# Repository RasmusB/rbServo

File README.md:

# rbServo Readme

### What is it?
All the hardware and software that is needed to build a CAN-BUS servo controller. It is meant to be used for RC servos.

### What does it contain?

- `3D` - hardware components

- `HW` - all the hardware design files are in this folder

- `SW` - The software for the servo.
 - `rbServoFirmware` - Servo controller firmware

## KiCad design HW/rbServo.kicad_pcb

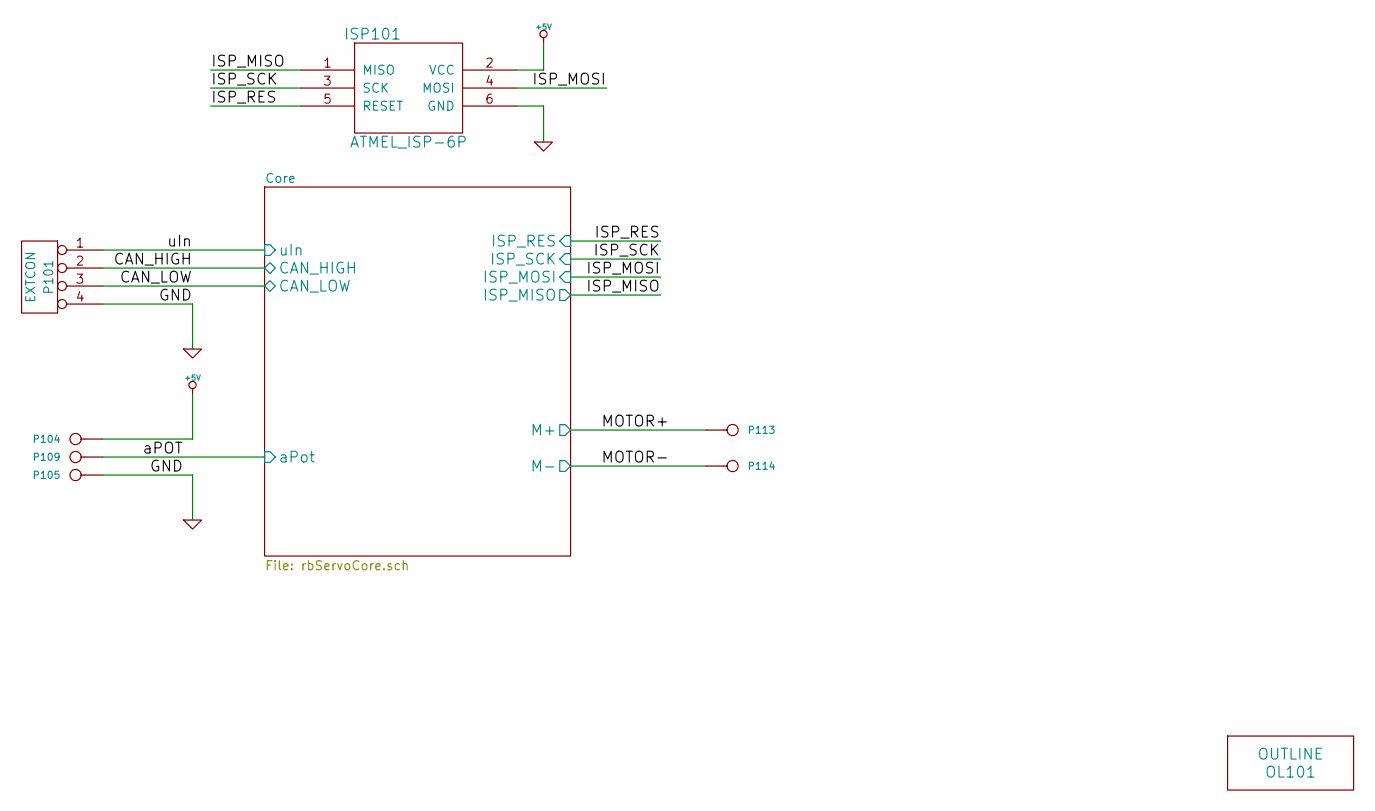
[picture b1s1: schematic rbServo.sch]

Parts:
ISP101: ATMEL_ISP-6P
OL101: OUTLINE
P101: EXTCON
P104: 5V
P105: GND
P109: Pot
P113: M+
P114: M-

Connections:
+5V: ISP101.2 (VCC), P104.1; also elsewhere on the board
/Core/CAN_HIGH: P101.2; also elsewhere on the board
/Core/CAN_LOW: P101.3; also elsewhere on the board
/Core/ISP_MISO: ISP101.1 (MISO); also elsewhere on the board
/Core/ISP_MOSI: ISP101.4 (MOSI); also elsewhere on the board
/Core/ISP_RES: ISP101.5 (RESET); also elsewhere on the board
/Core/ISP_SCK: ISP101.3 (SCK); also elsewhere on the board
/Core/M+: P113.1; also elsewhere on the board
/Core/M-: P114.1; also elsewhere on the board
/Core/aPot: P109.1; also elsewhere on the board
/Core/uIn: P101.1; also elsewhere on the board
GND: ISP101.6 (GND), P101.4, P105.1; also elsewhere on the board

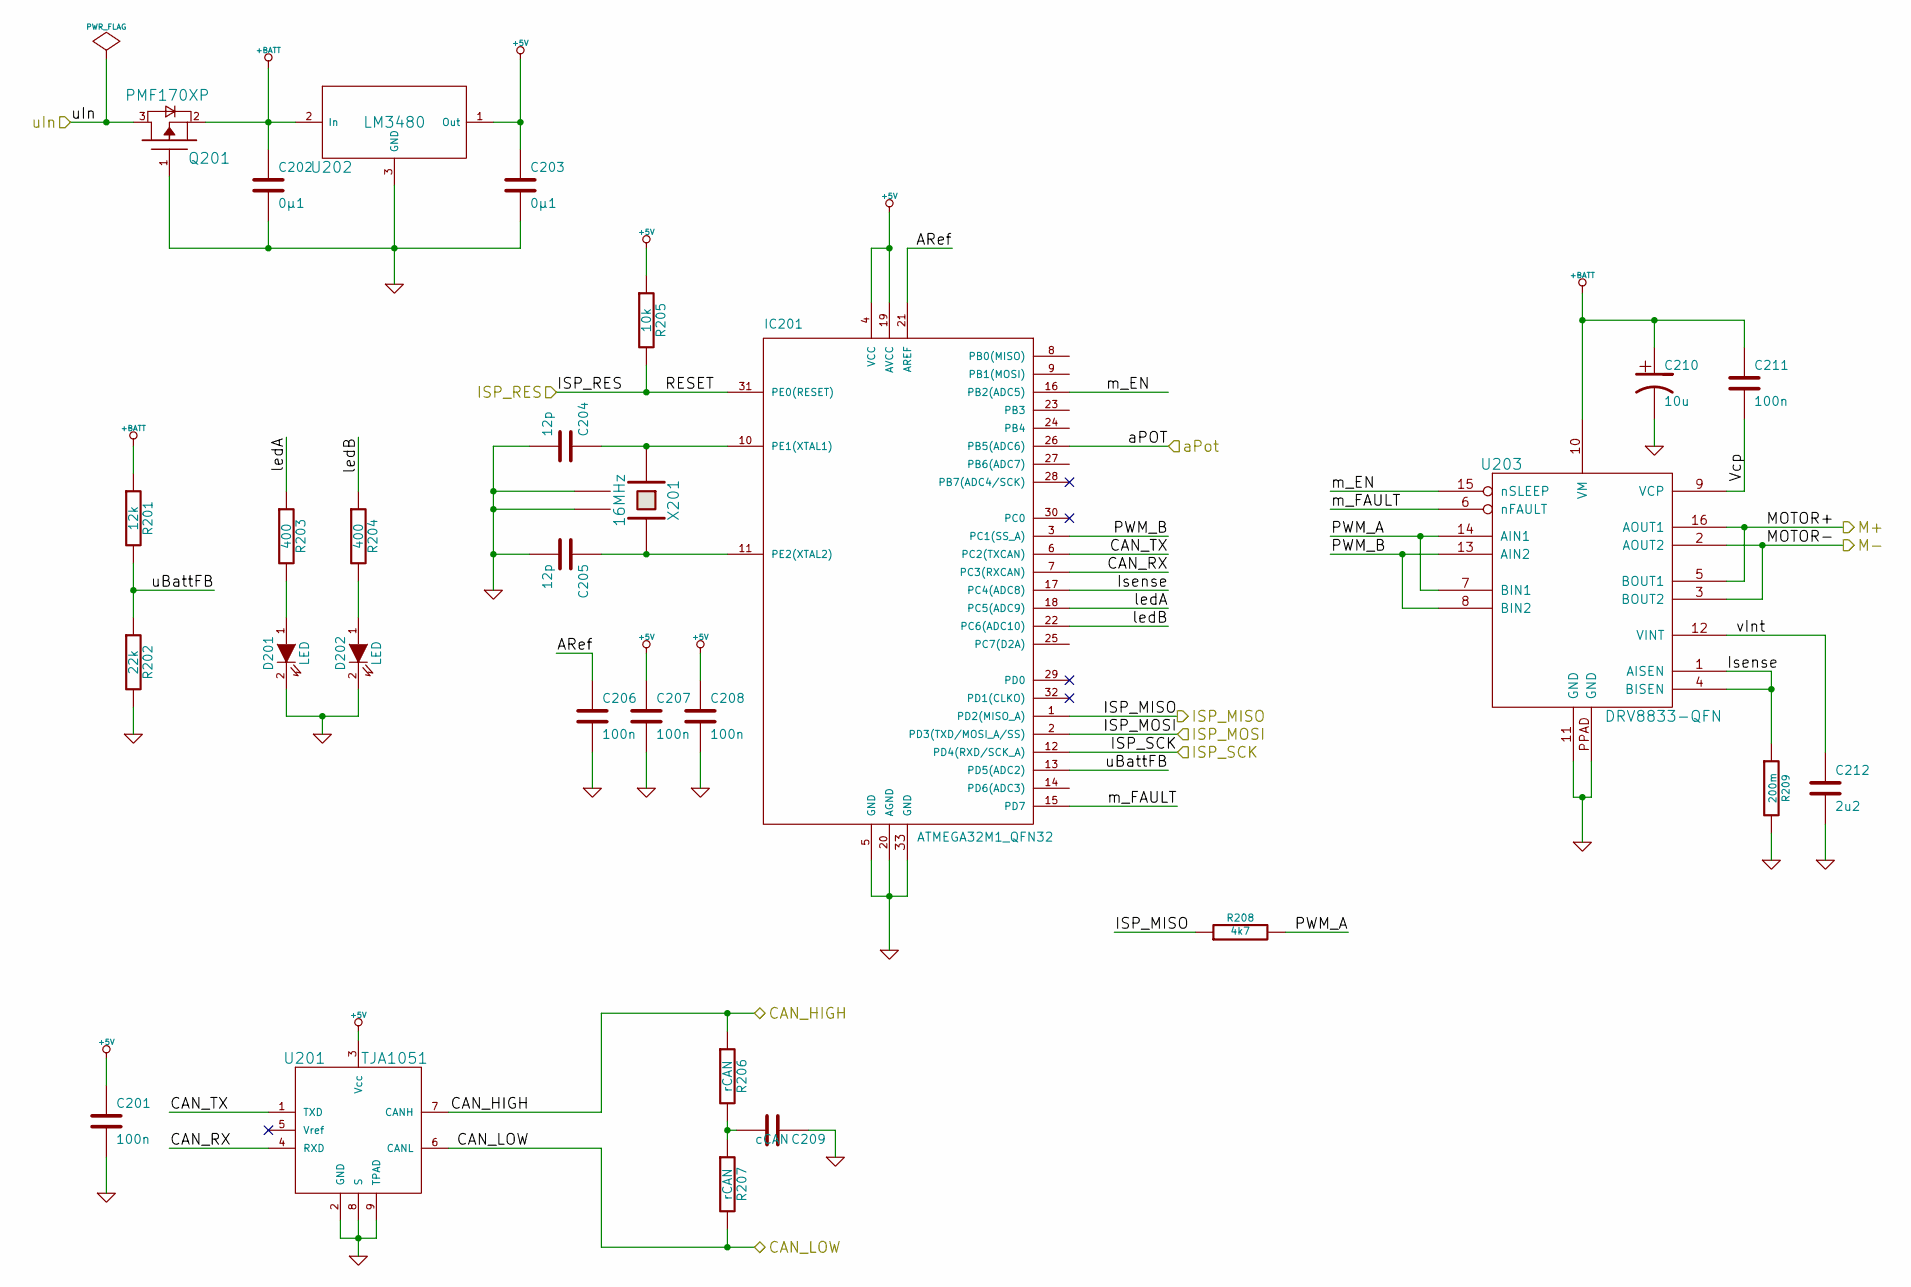
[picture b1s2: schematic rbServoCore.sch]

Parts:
C201, C206, C207, C208, C211: 100n
C202, C203: 0µ1
C204, C205: 12p
C209: cCAN
C210: 10u
C212: 2u2
D201, D202: LED
IC201: ATMEGA32M1_QFN32; MLF32
Q201: PMF170XP
R201: 12k
R202: 22k
R203, R204: 400
R205: 10k
R206, R207: rCAN
R208: 4k7
R209: 200m
U201: TJA1051
U202: LM3480; Mouser 926-LM3480IM35.0NOPB
U203: DRV8833-QFN
X201: 16MHz

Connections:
+5V: C201.1, C203.1, C207.1, C208.1, IC201.4 (VCC), IC201.19 (AVCC), R205.1, U201.3 (Vcc), U202.1 (Out); also elsewhere on the board
+BATT: C202.1, C210.1, C211.1, Q201.2 (S), R201.1, U202.2 (In), U203.10 (VM)
/Core/ARef: C206.1, IC201.21 (AREF)
/Core/CAN_HIGH: R206.1, U201.7 (CANH); also elsewhere on the board
/Core/CAN_LOW: R207.2, U201.6 (CANL); also elsewhere on the board
/Core/CAN_RX: IC201.7 (PC3(RXCAN)), U201.4 (RXD)
/Core/CAN_TX: IC201.6 (PC2(TXCAN)), U201.1 (TXD)
/Core/ISP_MISO: IC201.1 (PD2(MISO_A)), R208.1; also elsewhere on the board
/Core/ISP_MOSI: IC201.2 (PD3(TXD/MOSI_A/SS)); also elsewhere on the board
/Core/ISP_RES: IC201.31 (PE0(RESET)), R205.2; also elsewhere on the board
/Core/ISP_SCK: IC201.12 (PD4(RXD/SCK_A)); also elsewhere on the board
/Core/Isense: IC201.17 (PC4(ADC8)), R209.1, U203.1 (AISEN), U203.4 (BISEN)
/Core/M+: U203.5 (BOUT1), U203.16 (AOUT1); also elsewhere on the board
/Core/M-: U203.2 (AOUT2), U203.3 (BOUT2); also elsewhere on the board
/Core/PWM_A: R208.2, U203.7 (BIN1), U203.14 (AIN1)
/Core/PWM_B: IC201.3 (PC1(SS_A)), U203.8 (BIN2), U203.13 (AIN2)
/Core/Vcp: C211.2, U203.9 (VCP)
/Core/aPot: IC201.26 (PB5(ADC6)); also elsewhere on the board
/Core/ledA: IC201.18 (PC5(ADC9)), R203.1
/Core/ledB: IC201.22 (PC6(ADC10)), R204.1
/Core/m_EN: IC201.16 (PB2(ADC5)), U203.15 (nSLEEP)
/Core/m_FAULT: IC201.15 (PD7), U203.6 (nFAULT)
/Core/uBattFB: IC201.13 (PD5(ADC2)), R201.2, R202.1
/Core/uIn: Q201.3 (D); also elsewhere on the board
/Core/vInt: C212.1, U203.12 (VINT)
GND: C201.2, C202.2, C203.2, C204.2, C205.2, C206.2, C207.2, C208.2, C209.1, C210.2, C212.2, D201.2 (K), D202.2 (K), IC201.5 (GND), IC201.20 (AGND), IC201.33 (GND), Q201.1 (G), R202.2, R209.2, U201.2 (GND), U201.8 (S), U201.9 (TPAD), U202.3 (GND), U203.11 (GND), U203.PPAD (GND), X201.2 (GND), X201.4 (GND); also elsewhere on the board
unnamed: C204.1, IC201.10 (PE1(XTAL1)), X201.1
unnamed: C205.1, IC201.11 (PE2(XTAL2)), X201.3
unnamed: C209.2, R206.2, R207.1
unnamed: D201.1 (A), R203.2
unnamed: D202.1 (A), R204.2

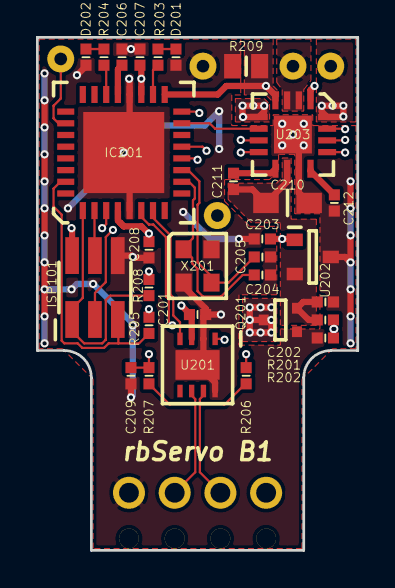
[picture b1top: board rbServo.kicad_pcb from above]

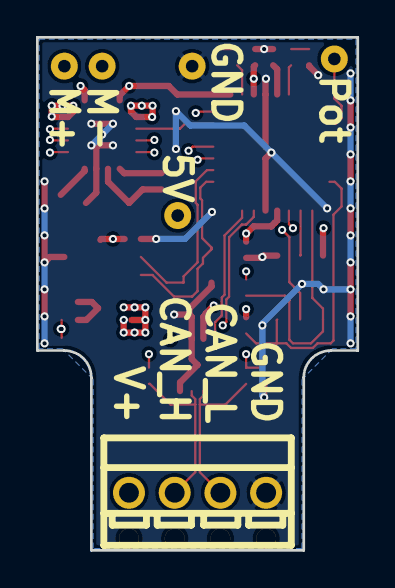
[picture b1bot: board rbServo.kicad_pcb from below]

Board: 4 copper layers, 17.8 x 28.5 mm, 37 parts (6 on the bottom side), 31 nets.

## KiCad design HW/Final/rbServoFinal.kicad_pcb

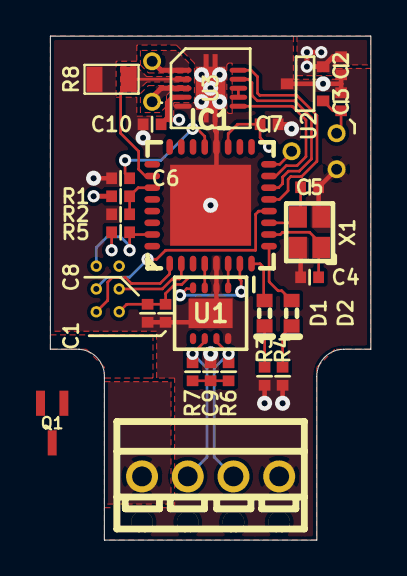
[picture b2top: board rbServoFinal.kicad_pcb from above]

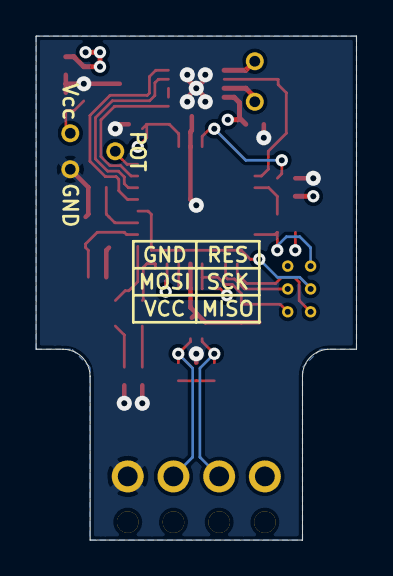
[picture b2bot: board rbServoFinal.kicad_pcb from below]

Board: 4 copper layers, 17.8 x 28.0 mm, 38 parts (9 on the bottom side), 29 nets.

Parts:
C1, C6, C7, C8, C10: 100n; SMD-R_1005_EIA0402-NOMINAL
C2, C3: 0µ1; SMD-R_1005_EIA0402-NOMINAL
C4, C5: 12p; SMD-R_1005_EIA0402-NOMINAL
C9: cCAN; SMD-R_1005_EIA0402-NOMINAL
D1, D2: LED; SMD-0603-LED
IC1: ATMEGA32M1_QFN32; QFN-32_0mm65
ISP1: MISO; HOLE_VIA-0mm635
ISP2: SCK; HOLE_VIA-0mm635
ISP3: RES; HOLE_VIA-0mm635
ISP4: VCC; HOLE_VIA-0mm635
ISP5: MOSI; HOLE_VIA-0mm635
ISP6: GND; HOLE_VIA-0mm635
M+1: +; connect_pin_header_1x1
M-1: -; connect_pin_header_1x1
P1: EXTCON; MPT_0,5/2,54x04
POT1: Vcc; connect_pin_header_1x1
POT2: POT; connect_pin_header_1x1
POT3: GND; connect_pin_header_1x1
Q1: PMF170XP; SOT323_SC-70-REFLOW
R1: 12k; SMD-R_1005_EIA0402-NOMINAL
R2: 22k; SMD-R_1005_EIA0402-NOMINAL
R3, R4: 400; SMD-R_1005_EIA0402-NOMINAL
R5: 10k; SMD-R_1005_EIA0402-NOMINAL
R6, R7: rCAN; SMD-R_1005_EIA0402-NOMINAL
R8: 200m; SMD-0805
U1: TJA1051; SOT782-1_HVSON8
U2: LM3480; SOT-23_TO-236AB
U3: DRV8832-DRC; S-PVSON-N10
X1: 16MHz; SMD-CX2520

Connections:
+5V: C1.1, C3.1, C7.1, C8.1, IC1.4, IC1.19, ISP4.1, POT1.1, R5.1, U1.3, U2.1
+BATT: C2.1, C10.1, Q1.2, R1.1, U2.2, U3.4
/Core/ARef: C6.1, IC1.21
/Core/CAN_HIGH: P1.3, R6.1, U1.7
/Core/CAN_LOW: P1.2, R7.2, U1.6
/Core/CAN_RX: IC1.7, U1.4
/Core/CAN_TX: IC1.6, U1.1
/Core/F_PWM: IC1.14, U3.9
/Core/ISP_MISO: IC1.1, ISP1.1
/Core/ISP_MOSI: IC1.2, ISP5.1
/Core/ISP_RES: IC1.31, ISP3.1, R5.2
/Core/ISP_SCK: IC1.12, ISP2.1
/Core/Isense: IC1.26, R8.1, U3.2
/Core/MOTOR+: M+1.1, U3.3
/Core/MOTOR-: M-1.1, U3.1
/Core/R_PWM: IC1.13, U3.10
/Core/aPot: IC1.16, POT2.1
/Core/ledA: D1.1, IC1.8
/Core/ledB: D2.1, IC1.9
/Core/m_EN: IC1.15, U3.6
/Core/uBattFB: IC1.27, R1.2, R2.1
/Core/uIn: P1.1, Q1.3
GND: C1.2, C2.2, C3.2, C4.2, C5.2, C6.2, C7.2, C8.2, C9.1, C10.2, IC1.5, IC1.20, IC1.33, ISP6.1, P1.4, POT3.1, Q1.1, R2.2, R3.2, R4.2, R8.2, U1.2, U1.8, U1.9, U2.3, U3.5, U3.PPAD, X1.2, X1.4
unnamed: C5.1, IC1.11, X1.3
unnamed: C4.1, IC1.10, X1.1
unnamed: U3.7, U3.8
unnamed: D1.2, R3.1
unnamed: D2.2, R4.1
unnamed: C9.2, R6.2, R7.1

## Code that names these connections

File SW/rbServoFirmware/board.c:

/*
The MIT License (MIT)

Copyright (c) 2014 Rasmus Backman

Permission is hereby granted, free of charge, to any person obtaining a copy
of this software and associated documentation files (the "Software"), to deal
in the Software without restriction, including without limitation the rights
to use, copy, modify, merge, publish, distribute, sublicense, and/or sell
copies of the Software, and to permit persons to whom the Software is
furnished to do so, subject to the following conditions:

The above copyright notice and this permission notice shall be included in all
copies or substantial portions of the Software.

THE SOFTWARE IS PROVIDED "AS IS", WITHOUT WARRANTY OF ANY KIND, EXPRESS OR
IMPLIED, INCLUDING BUT NOT LIMITED TO THE WARRANTIES OF MERCHANTABILITY,
FITNESS FOR A PARTICULAR PURPOSE AND NONINFRINGEMENT. IN NO EVENT SHALL THE
AUTHORS OR COPYRIGHT HOLDERS BE LIABLE FOR ANY CLAIM, DAMAGES OR OTHER
LIABILITY, WHETHER IN AN ACTION OF CONTRACT, TORT OR OTHERWISE, ARISING FROM,
OUT OF OR IN CONNECTION WITH THE SOFTWARE OR THE USE OR OTHER DEALINGS IN THE
SOFTWARE.
*/


#include <avr/io.h>
#include "board.h"
#include "timer.h"

#define RED_LED_PIN PC5
#define RED_LED_DDR DDRC
#define RED_LED_PORT PORTC

#define GRN_LED_PIN PC6
#define GRN_LED_DDR DDRC
#define GRN_LED_PORT PORTC

#define MOTOR_EN_PIN PB2
#define MOTOR_EN_DDR DDRB
#define MOTOR_EN_PORT PORTB

#define MOTOR_FAULT_PIN PD0
#define MOTOR_FAULT_DDR DDRD
#define MOTOR_FAULT_PORT PORTD

#define MOTOR_PWMA_PIN PD2
#define MOTOR_PWMA_DDR DDRD
#define MOTOR_PWMA_PORT PORTD

#define MOTOR_PWMB_PIN PC1
#define MOTOR_PWMB_DDR DDRC
#define MOTOR_PWMB_PORT PORTC

void boardInit () {

	RED_LED_DDR |= _BV(RED_LED_PIN);		// Normal output
	GRN_LED_DDR |= _BV(GRN_LED_PIN);		// Normal output
	MOTOR_EN_DDR |= _BV(MOTOR_EN_PIN);		// Normal output
	// MOTOR_FAULT_DDR is input by default
	MOTOR_PWMA_DDR |= _BV(MOTOR_PWMA_PIN);	// Controlled by HW PWM
	MOTOR_PWMB_DDR |= _BV(MOTOR_PWMB_PIN);	// Controlled by HW PWM
}

void boardMotorEnable() {

	MOTOR_EN_PORT |= _BV(MOTOR_EN_PIN);
}

void boardMotorDisable() {

	MOTOR_EN_PORT &= ~_BV(MOTOR_EN_PIN);
}

void redLEDon() {

	RED_LED_PORT |= _BV(RED_LED_PIN);
}

void redLEDoff() {

	RED_LED_PORT &= ~_BV(RED_LED_PIN);
}

void redLEDtoggle() {

	RED_LED_PORT ^= _BV(RED_LED_PIN);
}

void redLEDpwm( uint8_t dutyCycle ) {

	timerSetRedLEDdutyCycle ( dutyCycle );
}

void grnLEDon() {

	GRN_LED_PORT |= _BV(GRN_LED_PIN);
}

void grnLEDoff() {

	GRN_LED_PORT &= ~_BV(GRN_LED_PIN);
}

void grnLEDtoggle() {

	GRN_LED_PORT ^= _BV(GRN_LED_PIN);
}

void grnLEDpwm( uint8_t dutyCycle ) {

	timerSetGrnLEDdutyCycle ( dutyCycle );
}

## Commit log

2014-01-22 Initial commit, nothing useful yet
2014-03-11 Work on all fronts. The software is taking shape now.
2014-03-12 .gitignore updated to ignore all KiCAD temporary "BAK" files
2014-03-12 Remove unneeded PWM for now
2014-03-12 Cleanup in the HW directory. - The "proto", "final" and "common" directories are joined to one single design, based on the latest prototype design. - Readme.md updated to reflect this change
2014-03-13 Added simple software-based PWM for on board LED
2014-03-18 Trying new layout
2014-03-18 Started work on new servo lid for Tower Pro MG995 servo
2014-03-19 -Swapped CAN_H and CAN_L -Changed a few labels - All new layout that should fit i a servo
2014-03-22 New version of the servo lid. A debugger port hole needs to be added for a debugger compatible version.
2014-03-22 Work in progress on mechanical fit
2014-03-22 Servo lid model renamed for clarity
2014-03-22 Model structure tweaks
2014-03-22 Another revision of the servo body to document the modifications needed to fit the B1 PCB.
2014-03-23 Reshuffled file names again.
    No use having the filenames contain the version name when
    I'm using a version control system... doh!
2014-03-25 Added license and refactored
    - Added license information to source code (resolves issue #6)
    - Broke out ADC routines to own file
    - Broke out Timer interrupt handling to own file
    - Added EEPROM node configuration paramters
2014-03-26 Minor pin config additions
2014-08-27 Cleanup
